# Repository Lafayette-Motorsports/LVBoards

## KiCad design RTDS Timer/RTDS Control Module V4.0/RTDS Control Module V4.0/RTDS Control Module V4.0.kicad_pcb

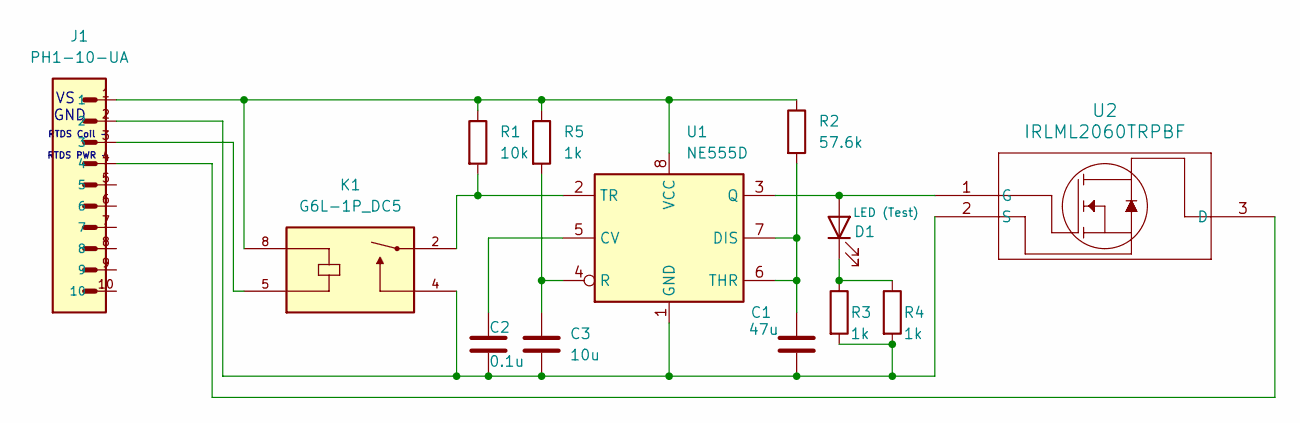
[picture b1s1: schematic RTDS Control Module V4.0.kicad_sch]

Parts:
C1: 47u; CAP_CL32_SAM
C2: 0.1u; CAP_CL31_SAM
C3: 10u; CAP_CL31_SAM
D1: LED (Test); LED_AP3216SYD_KNB
J1: PH1-10-UA; 1X10-2.54MM-THT
K1: G6L-1P_DC5; RELAY_G6L-1P_DC5
R1: 10k; STA_CF14_STP
R2: 57.6k; STA_CF14_STP
R3, R4: 1k; STA_RMCF0603_STP-L
R5: 1k; STA_CF14_STP
U1: NE555D; SOIC-8_3.9x4.9mm_P1.27mm
U2: IRLML2060TRPBF; SOT23_INF

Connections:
unnamed: D1.2 (A), U1.3 (Q), U2.1 (G)
unnamed: D1.1 (K), R3.1, R4.1
unnamed: J1.3, K1.5
unnamed: C2.1, U1.5 (CV)
unnamed: C1.1, R2.2, U1.6 (THR), U1.7 (DIS)
unnamed: C1.2, C2.2, C3.2, J1.2, K1.4, R3.2, R4.2, U1.1 (GND), U2.2 (S)
unnamed 6: J1.1, K1.8, R1.1, R2.1, R5.1, U1.8 (VCC); also elsewhere on the board
unnamed: K1.2, R1.2, U1.2 (TR)
unnamed: J1.4, U2.3 (D)
RESET: C3.1, R5.2, U1.4 (R); also elsewhere on the board

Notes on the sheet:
RTDS PWR -
GND
RTDS Coil -

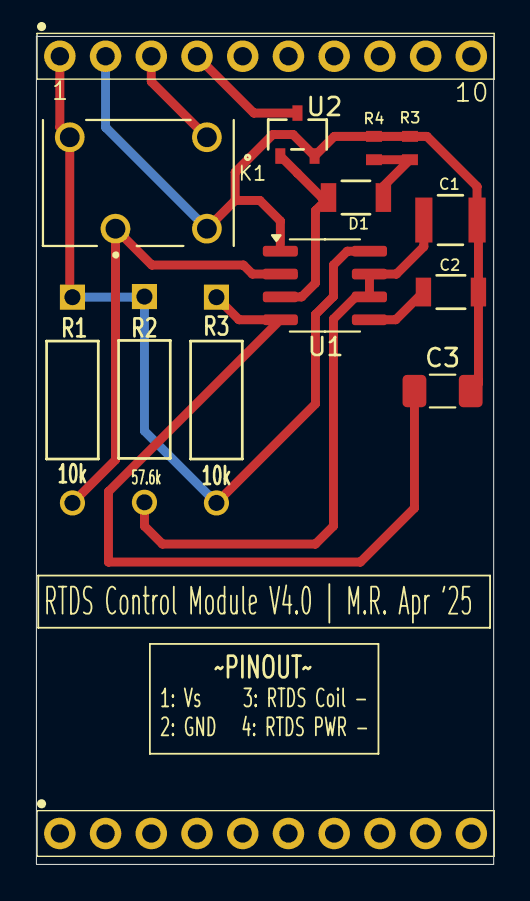
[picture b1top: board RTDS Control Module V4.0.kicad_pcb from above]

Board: 2 copper layers, 25.4 x 46.0 mm, 14 parts (0 on the bottom side), 10 nets.

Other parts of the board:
J2: PH1-10-UA; 1X10-2.54MM-THT
R3#2: 10k; STA_CF14_STP

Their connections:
unnamed 6: R3#2.2; also elsewhere on the board
RESET: R3#2.1; also elsewhere on the board

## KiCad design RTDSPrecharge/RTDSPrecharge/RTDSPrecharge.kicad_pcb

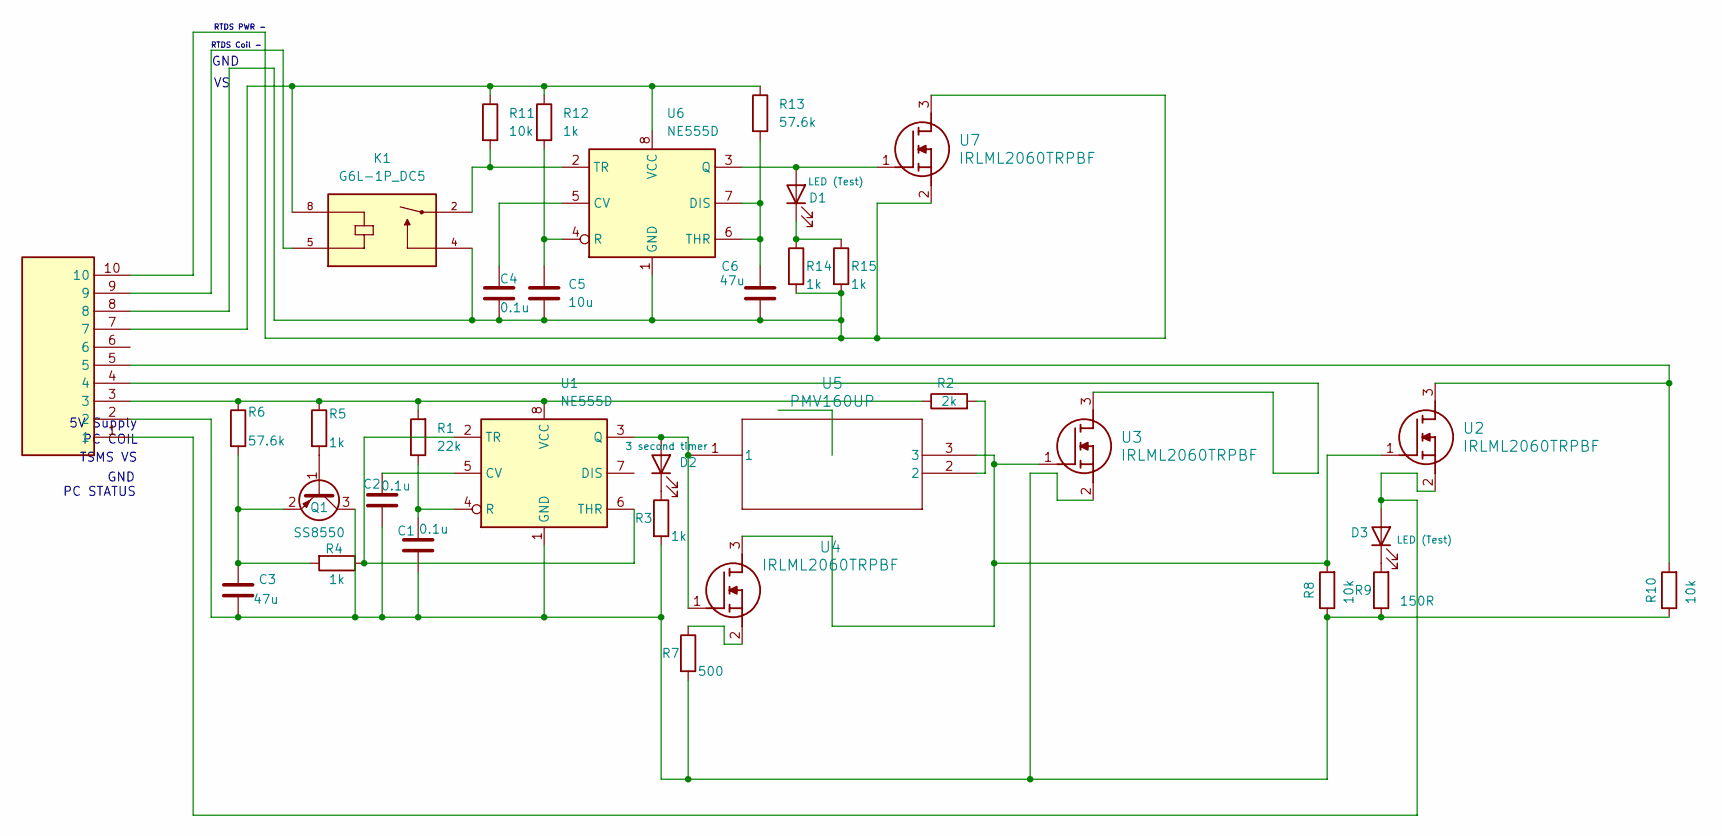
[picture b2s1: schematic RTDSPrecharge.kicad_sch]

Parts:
C1, C2, C4: 0.1u; C_0201_0603Metric
C3, C6: 47u; C_0201_0603Metric
C5: 10u; C_0201_0603Metric
D1, D3: LED (Test); LED_AP3216SYD_KNB
D2: 3 second timer; LED_AP3216SYD_KNB
J1: PH1-10-UA; HDRV10W64P0X254_1X10_2540X249X886P; Manufacturer_Part_Number PH1-10-UA; Mouser Part Number 737-PH1-10-UA
K1: G6L-1P_DC5; RELAY_G6L-1P_DC5
Q1: SS8550; SOT95P237X112-3N
R1: 22k; STA_CF14_STP
R2: 2k; STA_CF14_STP
R3, R4, R5, R12, R14, R15: 1k; STA_CF14_STP
R6, R13: 57.6k; STA_CF14_STP
R7: 500; STA_CF14_STP
R8, R10, R11: 10k; STA_CF14_STP
R9: 150R; STA_CF14_STP
U1: NE555D; SOIC127P599X175-8N
U2, U3, U4, U7: IRLML2060TRPBF; SOT95P237X112-3N; Manufacturer_Part_Number IRLML2060TRPBF; Mouser Part Number 942-IRLML2060TRPBF
U5: PMV160UP; SOT95P230X110-3N
U6: NE555D; SOIC-8_3.9x4.9mm_P1.27mm

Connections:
unnamed: D1.2 (A), U6.3 (Q), U7.1 (G)
unnamed: D1.1 (K), R14.1, R15.1
unnamed: D2.2 (A), U1.3 (Q), U4.1 (G), U5.1
unnamed: D2.1 (K), R3.1
unnamed: D3.2 (A), J1.1, U2.2 (S)
unnamed: D3.1 (K), R9.2
unnamed: J1.9, K1.5
unnamed: Q1.1 (B), R5.2
unnamed: C1.2, C2.2, C3.2, J1.2, Q1.3 (C), R3.2, R7.2, R8.1, R9.1, R10.1, U1.1 (GND), U3.2 (S)
unnamed: C3.1, Q1.2 (E), R4.2, R6.2
unnamed: R2.2, U5.2
unnamed: C2.1, U1.5 (CV)
unnamed: C1.1, R1.1, U1.4 (R)
unnamed: R4.1, U1.2 (TR), U1.6 (THR)
unnamed: J1.3, R1.2, R2.1, R5.1, R6.1, U1.8 (VCC)
unnamed: J1.5, R10.2, U2.3 (D)
unnamed: R8.2, U2.1 (G), U3.1 (G), U4.3 (D), U5.3
unnamed: J1.4, U3.3 (D)
unnamed: R7.1, U4.2 (S)
unnamed: C4.1, U6.5 (CV)
unnamed: C6.1, R13.2, U6.6 (THR), U6.7 (DIS)
unnamed: C4.2, C5.2, C6.2, J1.8, J1.10, K1.4, R14.2, R15.2, U6.1 (GND), U7.2 (S), U7.3 (D)
unnamed: C5.1, R12.2, U6.4 (R)
unnamed: K1.2, R11.2, U6.2 (TR)
unnamed: J1.7, K1.8, R11.1, R12.1, R13.1, U6.8 (VCC)

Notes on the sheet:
RTDS Coil -
RTDS PWR -
PC COIL
GND
TSMS VS
5V Supply
GND
PC STATUS

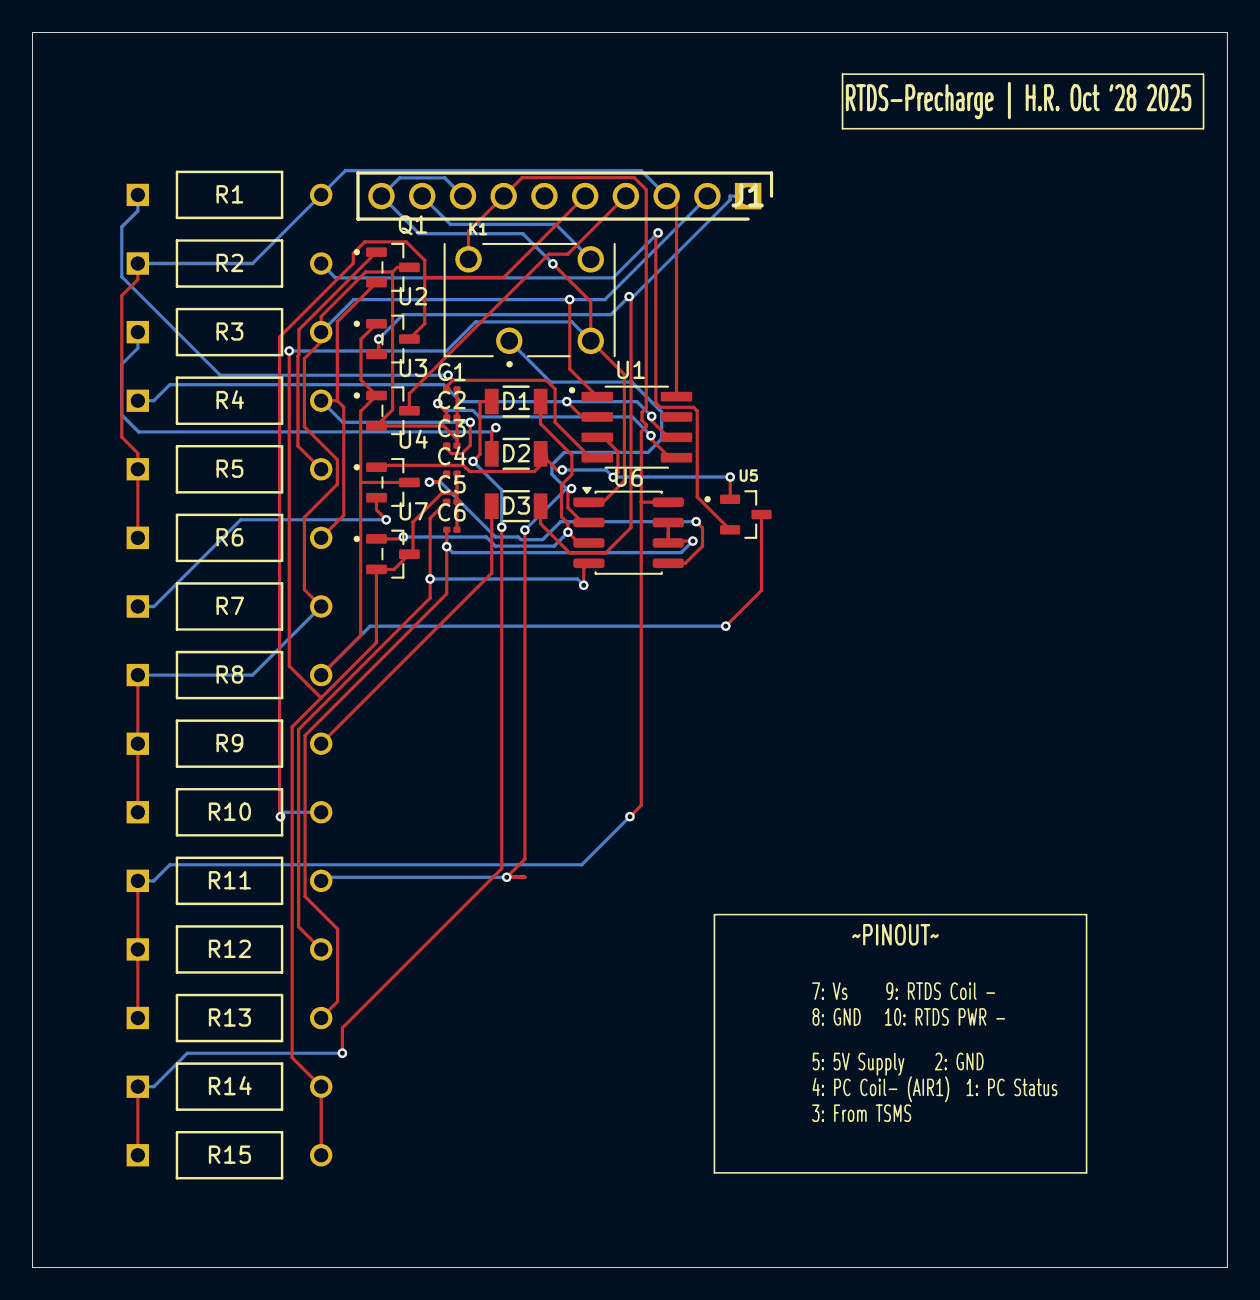
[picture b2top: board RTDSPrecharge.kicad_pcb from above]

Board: 2 copper layers, 74.5 x 77.0 mm, 34 parts (0 on the bottom side), 25 nets.

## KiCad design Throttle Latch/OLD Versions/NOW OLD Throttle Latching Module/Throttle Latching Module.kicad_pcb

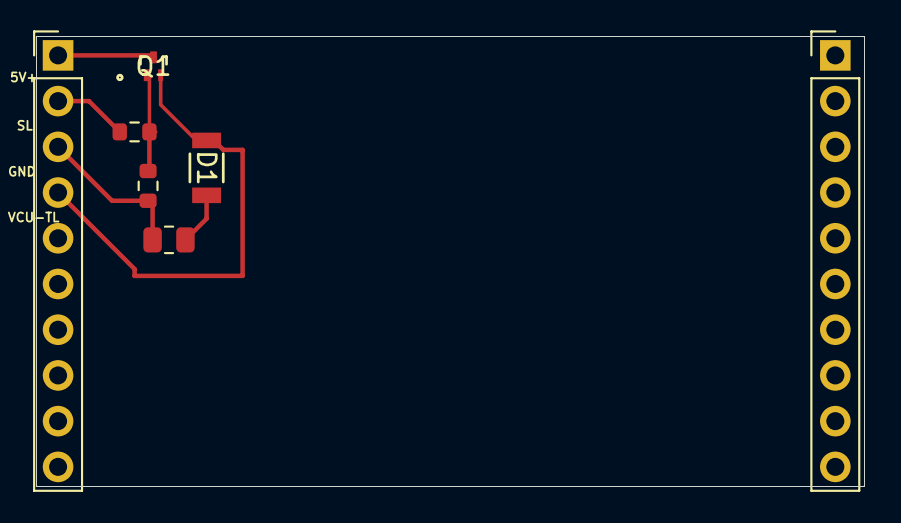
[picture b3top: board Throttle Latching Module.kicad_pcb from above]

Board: 2 copper layers, 46.0 x 25.0 mm, 7 parts (0 on the bottom side), 6 nets.

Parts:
D1: LED (Test); LED_AP3216SYD_KNB
J1, J1#2: PH1-10-UA; PinHeader_1x10_P2.54mm_Vertical
Q1: SSM3J56MFV; VESM_TOS
R1: 150R; R_0805_2012Metric
R2, R3: 10k; R_0603_1608Metric

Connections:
unnamed: D1.2 (A), J1.4
unnamed: D1.1 (K), Q1.2 (S), R1.2
unnamed: J1.2, R2.1
unnamed: J1.3, R1.1, R3.1
unnamed: J1.1, Q1.3 (D)
unnamed: Q1.1 (G), R2.2, R3.2

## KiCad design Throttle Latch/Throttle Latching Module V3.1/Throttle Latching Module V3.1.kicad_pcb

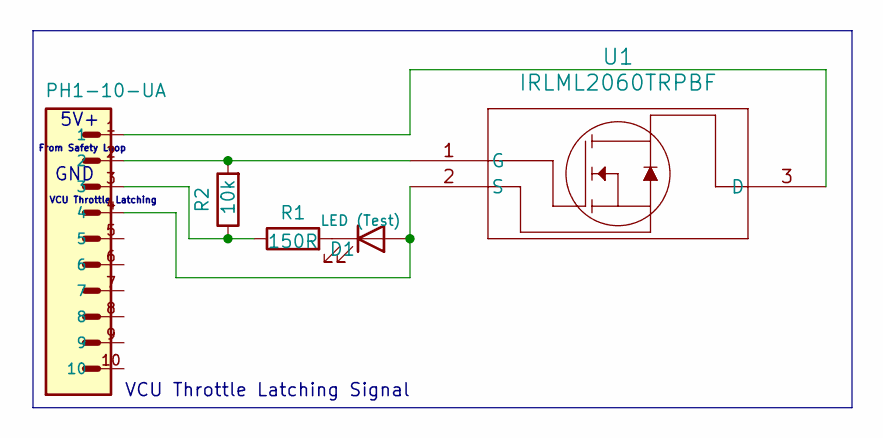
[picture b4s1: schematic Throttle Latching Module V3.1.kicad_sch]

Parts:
D1: LED (Test); LED_AP3216SYD_KNB
J1: PH1-10-UA; 1X10-2.54MM-THT
R1: 150R; STA_CF14_STP
R2: 10k; STA_CF14_STP
U1: IRLML2060TRPBF; SOT23_INF

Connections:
unnamed: D1.2 (A), J1.4, U1.2 (S)
unnamed: D1.1 (K), R1.2
unnamed: J1.3, R1.1, R2.1
unnamed: J1.1, U1.3 (D)
unnamed: J1.2, R2.2, U1.1 (G)

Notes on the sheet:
5V+
VCU Throttle Latching
VCU Throttle Latching Signal
From Safety Loop
GND

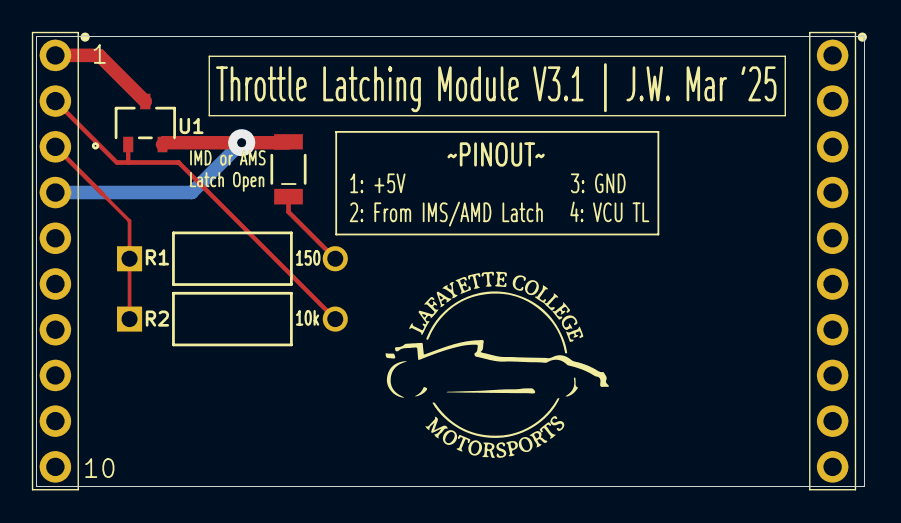
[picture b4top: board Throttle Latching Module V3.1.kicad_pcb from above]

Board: 2 copper layers, 46.0 x 25.0 mm, 6 parts (0 on the bottom side), 5 nets.

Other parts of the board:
J2: PH1-10-UA; 1X10-2.54MM-THT
